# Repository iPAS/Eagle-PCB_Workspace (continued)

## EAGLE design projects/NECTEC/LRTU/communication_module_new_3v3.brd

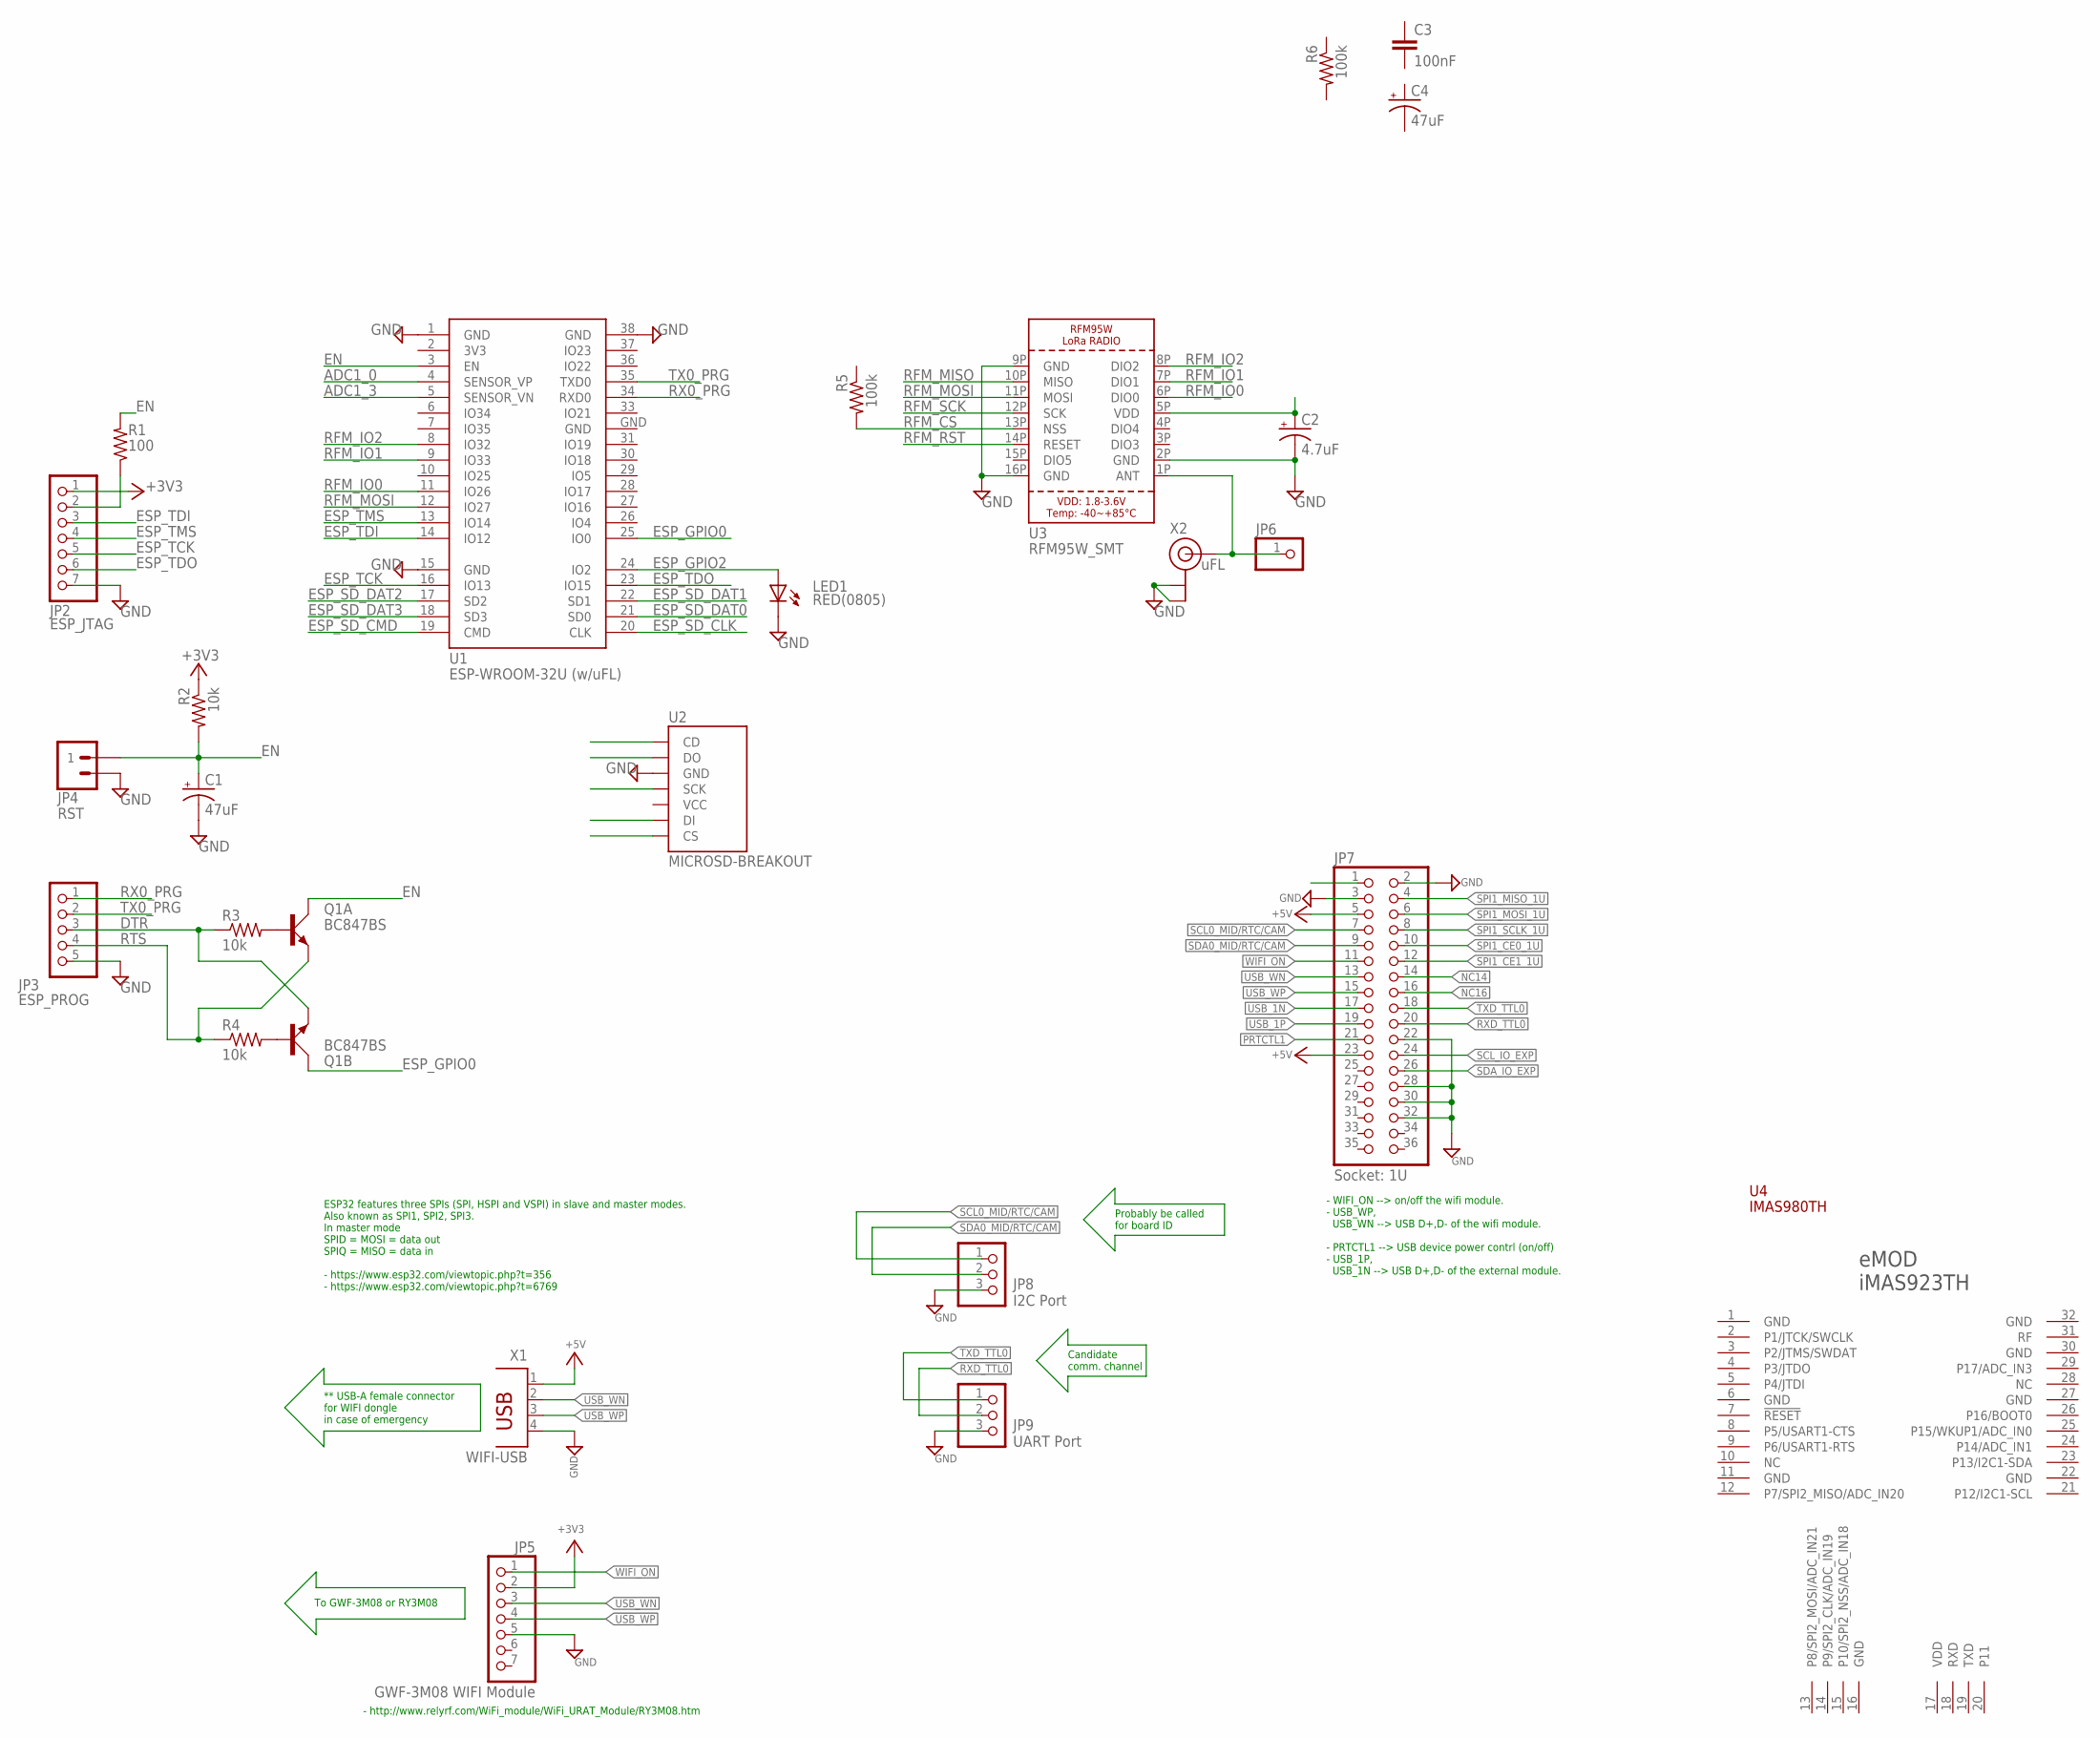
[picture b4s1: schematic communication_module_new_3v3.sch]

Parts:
C1, C4: 47uF; RCL_150CLZ-1014
C2: 4.7uF; RCL_150CLZ-1014
C3: 100nF; RCL_C1206
JP2: ESP_JTAG; 1X07
JP3: ESP_PROG; 1X05
JP4: RST; 1X02
JP5: GWF-3M08 WIFI Module; 1X07
JP6: HEADER-1X1ROUND; 1X01_ROUND
JP7: Socket: 1U; 2X18
JP8: I2C Port; 1X03
JP9: UART Port; 1X03
LED1: RED(0805); CHIP-LED0805
Q1: BC847BS; SOT363_PHILIPS
R1: 100; RCL_M0805
R2, R3, R4: 10k; RCL_M0805
R5, R6: 100k; RCL_M0805
U1: ESP-WROOM-32U (w/uFL); ESP-WROOM-32
U2: MICROSD-BREAKOUT
U3: RFM95W_SMT; RFMHCW_SMT
U4: IMAS980TH; IMAS923TH
X1: WIFI-USB; PN87520
X2: uFL; U.FL

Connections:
3V3: U1.2 (3V3)
+3V3: JP2.1, JP5.2, R2.1
+5V: JP7.5, JP7.23, X1.1
ADC1_0: U1.4 (SENSOR_VP)
ADC1_3: U1.5 (SENSOR_VN)
ANT: JP6.1, U3.1P (ANT), X2.3 (SIGNAL)
DTR: JP3.3, Q1.4 (E), R3.1
EN: C1.+, JP4.1, Q1.6 (C), R1.2, R2.2, U1.3 (EN)
ESP_GPIO0: Q1.3 (C), U1.25 (IO0)
ESP_GPIO2: LED1.A, U1.24 (IO2)
ESP_SD_CLK: U1.20 (CLK)
ESP_SD_CMD: U1.19 (CMD)
ESP_SD_DAT0: U1.21 (SD0)
ESP_SD_DAT1: U1.22 (SD1)
ESP_SD_DAT2: U1.17 (SD2)
ESP_SD_DAT3: U1.18 (SD3)
ESP_TCK: JP2.5, U1.16 (IO13)
ESP_TDI: JP2.3, U1.14 (IO12)
ESP_TDO: JP2.6, U1.23 (IO15)
ESP_TMS: JP2.4, U1.13 (IO14)
GND: C1.-, C2.-, JP2.7, JP3.5, JP4.2, JP5.5, JP7.2, JP7.3, JP7.22, JP7.28, JP7.30, JP7.32, JP8.3, JP9.3, LED1.C, U1.1 (GND), U1.15 (GND), U1.38 (GND), U1.GND, U2.GND, U3.2P (GND), U3.9P (GND), U3.16P (GND), U4.1 (GND), U4.6 (GND), U4.11 (GND), U4.16 (GND), U4.22 (GND), U4.27 (GND), U4.30 (GND), U4.32 (GND), X1.4, X2.1 (GND), X2.2 (GND)
unnamed: C2.+, U3.5P (VDD)
unnamed: Q1.2 (B), R3.2
unnamed: Q1.5 (B), R4.2
unnamed: JP2.2, R1.1
NC14: JP7.14
NC16: JP7.16
PRTCTL1: JP7.21
RFM_CS: R5.2, U3.13P (NSS)
RFM_IO0: U1.11 (IO26), U3.6P (DIO0)
RFM_IO1: U1.9 (IO33), U3.7P (DIO1)
RFM_IO2: U1.8 (IO32), U3.8P (DIO2)
RFM_MISO: U3.10P (MISO)
RFM_MOSI: U1.12 (IO27), U3.11P (MOSI)
RFM_RST: U3.14P (RESET)
RFM_SCK: U3.12P (SCK)
RTS: JP3.4, Q1.1 (E), R4.1
RX0_PRG: JP3.1, U1.34 (RXD0)
RXD_TTL0: JP7.20, JP9.2
SCL0_MID/RTC/CAM: JP7.7, JP8.1
SCL_IO_EXP: JP7.24
SDA0_MID/RTC/CAM: JP7.9, JP8.2
SDA_IO_EXP: JP7.26
SPI1_CE0_1U: JP7.10
SPI1_CE1_1U: JP7.12
SPI1_MISO_1U: JP7.4
SPI1_MOSI_1U: JP7.6
SPI1_SCLK_1U: JP7.8
TX0_PRG: JP3.2, U1.35 (TXD0)
TXD_TTL0: JP7.18, JP9.1
USB_1N: JP7.17
USB_1P: JP7.19
USB_WN: JP5.3, JP7.13, X1.2
USB_WP: JP5.4, JP7.15, X1.3
VDD: U4.17 (VDD)
WIFI_ON: JP5.1, JP7.11

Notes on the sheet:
ESP32 features three SPIs (SPI, HSPI and VSPI) in slave and master modes. Also known as SPI1, SPI2, SPI3. In master mode SPID = MOSI = data out SPIQ = MISO = data in - https://www.esp32.com/viewtopic.php?t=356 - https://www.esp32.com/viewtopic.php?t=6769
- WIFI_ON --> on/off the wifi module. - USB_WP, USB_WN --> USB D+,D- of the wifi module. - PRTCTL1 --> USB device power contrl (on/off) - USB_1P, USB_1N --> USB D+,D- of the external module.
** USB-A female connector for WIFI dongle in case of emergency
Probably be called for board ID
Candidate comm. channel
To GWF-3M08 or RY3M08
- http://www.relyrf.com/WiFi_module/WiFi_URAT_Module/RY3M08.htm

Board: 2 copper layers, 26 parts (0 on the bottom side), 31 nets, no tracks yet.

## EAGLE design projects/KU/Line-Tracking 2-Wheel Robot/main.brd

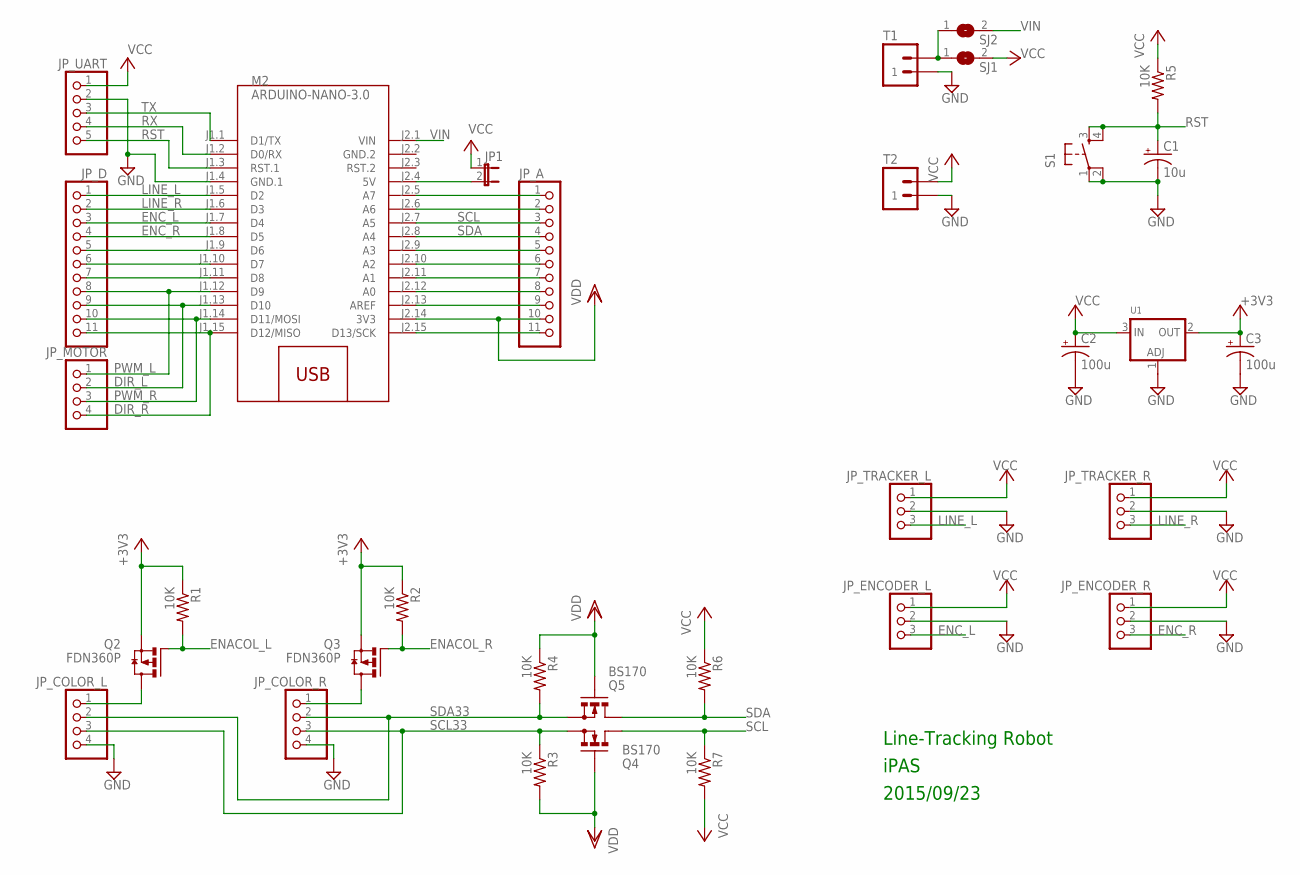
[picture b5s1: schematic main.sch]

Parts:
C1: 10u; RCL_E2,5-6
C2, C3: 100u; RCL_E2,5-6
JP1: JUMPER2
JP_A: HEADER-1X11; 1X11_ROUND
JP_COLOR_L: HEADER-1X4ROUND; 1X04_ROUND
JP_COLOR_R: HEADER-1X4ROUND; 1X04_ROUND
JP_D: HEADER-1X11; 1X11_ROUND
JP_ENCODER_L: HEADER-1X3ROUND; 1X03_ROUND
JP_ENCODER_R: HEADER-1X3ROUND; 1X03_ROUND
JP_MOTOR: HEADER-1X4ROUND; 1X04_ROUND
JP_TRACKER_L: HEADER-1X3ROUND; 1X03_ROUND
JP_TRACKER_R: HEADER-1X3ROUND; 1X03_ROUND
JP_UART: HEADER-1X5ROUND; 1X05_ROUND
M2: ARDUINO-NANO-3.0
Q2, Q3: FDN360P; SUPER-SOT3
Q4, Q5: BS170; TO92-
R1, R2, R3, R4, R5, R6, R7: 10K; RCL_0204/5
S1: SWITCH-TACT_DTS-6
SJ1, SJ2: SOLDERJUMPERREFLOW; SOLDERJUMPER_REFLOW
T1, T2: ST02-3.81MM; DG381-02P
U1: LM1117SOT223-REFLOW; SOT223-R

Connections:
+3V3: C3.+, Q2.2 (S), Q3.2 (S), R1.1, R2.1, U1.2 (OUT)
DIR_L: JP_D.9, JP_MOTOR.2, M2.J1.13 (D10)
DIR_R: JP_D.11, JP_MOTOR.4, M2.J1.15 (D12/MISO)
ENACOL_L: Q2.1 (G), R1.2
ENACOL_R: Q3.1 (G), R2.2
ENC_L: JP_D.3, JP_ENCODER_L.3, M2.J1.7 (D4)
ENC_R: JP_D.4, JP_ENCODER_R.3, M2.J1.8 (D5)
GND: C1.-, C2.-, C3.-, JP_COLOR_L.4, JP_COLOR_R.4, JP_ENCODER_L.2, JP_ENCODER_R.2, JP_TRACKER_L.2, JP_TRACKER_R.2, JP_UART.2, M2.J1.4 (GND.1), S1.1, S1.2, T1.1, T2.1, U1.1 (ADJ)
GND.2: M2.J2.2 (GND.2)
LINE_L: JP_D.1, JP_TRACKER_L.3, M2.J1.5 (D2)
LINE_R: JP_D.2, JP_TRACKER_R.3, M2.J1.6 (D3)
unnamed: JP_COLOR_R.1, Q3.3 (D)
unnamed: JP_A.1, M2.J2.5 (A7)
unnamed: JP_COLOR_L.1, Q2.3 (D)
unnamed: JP_A.2, M2.J2.6 (A6)
unnamed: JP1.2, M2.J2.4 (5V)
unnamed: SJ1.1, SJ2.1, T1.2
unnamed: JP_D.5, M2.J1.9 (D6)
unnamed: JP_D.6, M2.J1.10 (D7)
unnamed: JP_D.7, M2.J1.11 (D8)
unnamed: JP_A.5, M2.J2.9 (A3)
unnamed: JP_A.6, M2.J2.10 (A2)
unnamed: JP_A.7, M2.J2.11 (A1)
unnamed: JP_A.8, M2.J2.12 (A0)
unnamed: JP_A.9, M2.J2.13 (AREF)
unnamed: JP_A.11, M2.J2.15 (D13/SCK)
PWM_L: JP_D.8, JP_MOTOR.1, M2.J1.12 (D9)
PWM_R: JP_D.10, JP_MOTOR.3, M2.J1.14 (D11/MOSI)
RST: C1.+, JP_UART.5, M2.J1.3 (RST.1), R5.2, S1.3, S1.4
RX: JP_UART.4, M2.J1.2 (D0/RX)
SCL: JP_A.3, M2.J2.7 (A5), Q4.1 (D), R7.1
SCL33: JP_COLOR_L.3, JP_COLOR_R.3, Q4.3 (S), R3.1
SDA: JP_A.4, M2.J2.8 (A4), Q5.1 (D), R6.2
SDA33: JP_COLOR_L.2, JP_COLOR_R.2, Q5.3 (S), R4.2
TX: JP_UART.3, M2.J1.1 (D1/TX)
VCC: C2.+, JP1.1, JP_ENCODER_L.1, JP_ENCODER_R.1, JP_TRACKER_L.1, JP_TRACKER_R.1, JP_UART.1, R5.1, R6.1, R7.2, SJ1.2, T2.2, U1.3 (IN)
VDD: JP_A.10, M2.J2.14 (3V3), Q4.2 (G), Q5.2 (G), R3.2, R4.1
VIN: M2.J2.1 (VIN), SJ2.2

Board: 2 copper layers, 32 parts (0 on the bottom side), 37 nets, no tracks yet.

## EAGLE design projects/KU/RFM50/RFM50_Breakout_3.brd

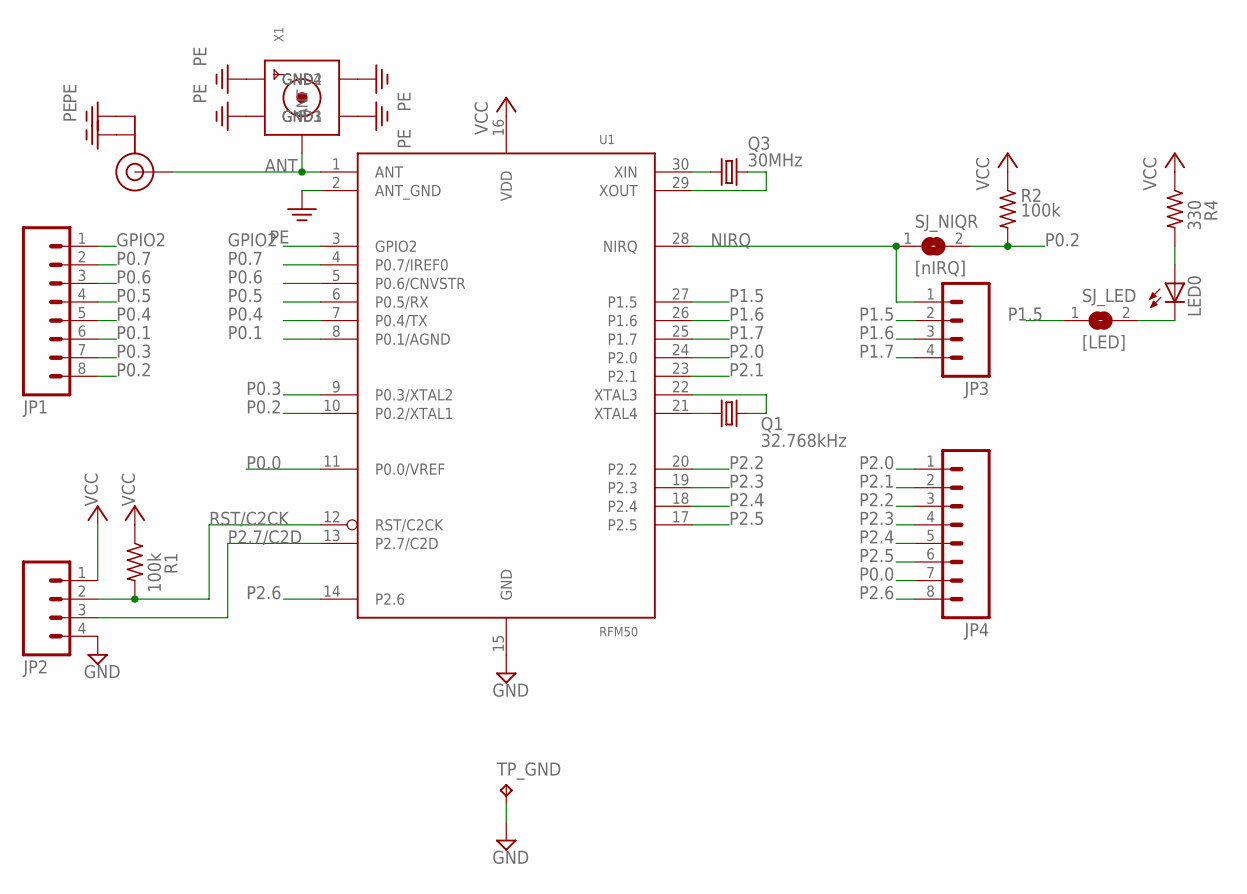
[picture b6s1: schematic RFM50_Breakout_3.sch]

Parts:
JP1, JP4: M081X08; 1X08
JP2, JP3: M04PTH; 1X04
LED0: LED3MM
Q1: 32.768kHz; TC26H
Q3: 30MHz; HC49/S
R1: 100k; RCL_0204/7
R2: 100k; RCL_M1206
R4: 330; RCL_0204/5
SJ_LED: [LED]; SOLDERJUMPER_REFLOW
SJ_NIQR: [nIRQ]; SOLDERJUMPER_REFLOW
TP_GND: TPPAD1-10; P1-10_TP
U1: RFM50
U$1: U.FL
X1: SMACONNECTOR; SMA90_DIP

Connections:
ANT: U1.1 (ANT), U$1.P$3 (SIGNAL), X1.ANTENNA (ANT)
GND: JP2.4, TP_GND.TP, U1.15 (GND)
GPIO2: JP1.1, U1.3 (GPIO2)
unnamed: LED0.A, R4.2
unnamed: LED0.K (C), SJ_LED.2
unnamed: Q1.1, U1.21 (XTAL4)
unnamed: Q3.1, U1.30 (XIN)
unnamed: Q3.2, U1.29 (XOUT)
unnamed: Q1.2, U1.22 (XTAL3)
NIRQ: JP3.1, SJ_NIQR.1, U1.28 (NIRQ)
P0.0: JP4.7, U1.11 (P0.0/VREF)
P0.1: JP1.6, U1.8 (P0.1/AGND)
P0.2: JP1.8, R2.2, SJ_NIQR.2, U1.10 (P0.2/XTAL1)
P0.3: JP1.7, U1.9 (P0.3/XTAL2)
P0.4: JP1.5, U1.7 (P0.4/TX)
P0.5: JP1.4, U1.6 (P0.5/RX)
P0.6: JP1.3, U1.5 (P0.6/CNVSTR)
P0.7: JP1.2, U1.4 (P0.7/IREF0)
P1.5: JP3.2, SJ_LED.1, U1.27 (P1.5)
P1.6: JP3.3, U1.26 (P1.6)
P1.7: JP3.4, U1.25 (P1.7)
P2.0: JP4.1, U1.24 (P2.0)
P2.1: JP4.2, U1.23 (P2.1)
P2.2: JP4.3, U1.20 (P2.2)
P2.3: JP4.4, U1.19 (P2.3)
P2.4: JP4.5, U1.18 (P2.4)
P2.5: JP4.6, U1.17 (P2.5)
P2.6: JP4.8, U1.14 (P2.6)
P2.7/C2D: JP2.3, U1.13 (P2.7/C2D)
PE: U1.2 (ANT_GND), U$1.P$1 (GND), U$1.P$2 (GND), X1.GND1, X1.GND2, X1.GND3, X1.GND4
RST/C2CK: JP2.2, R1.2, U1.12 (RST/C2CK)
VCC: JP2.1, R1.1, R2.1, R4.1, U1.16 (VDD)

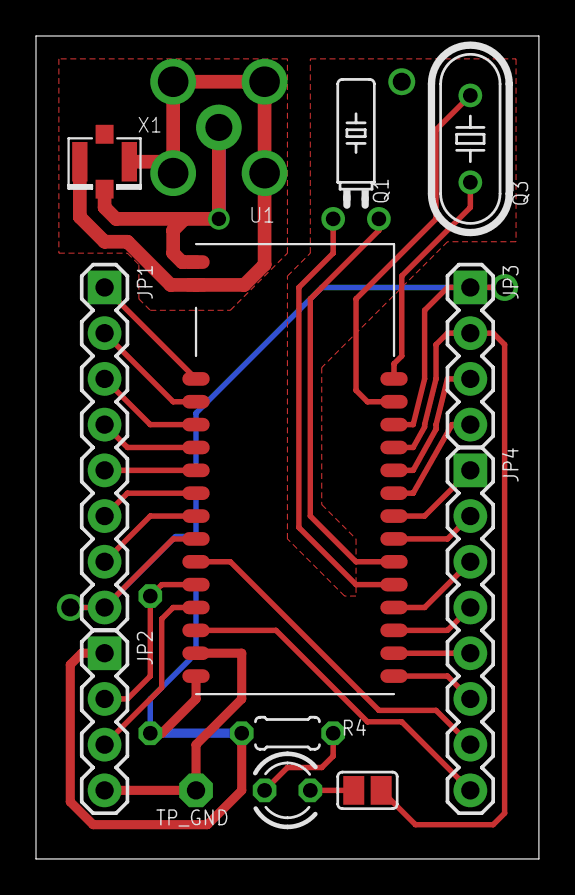
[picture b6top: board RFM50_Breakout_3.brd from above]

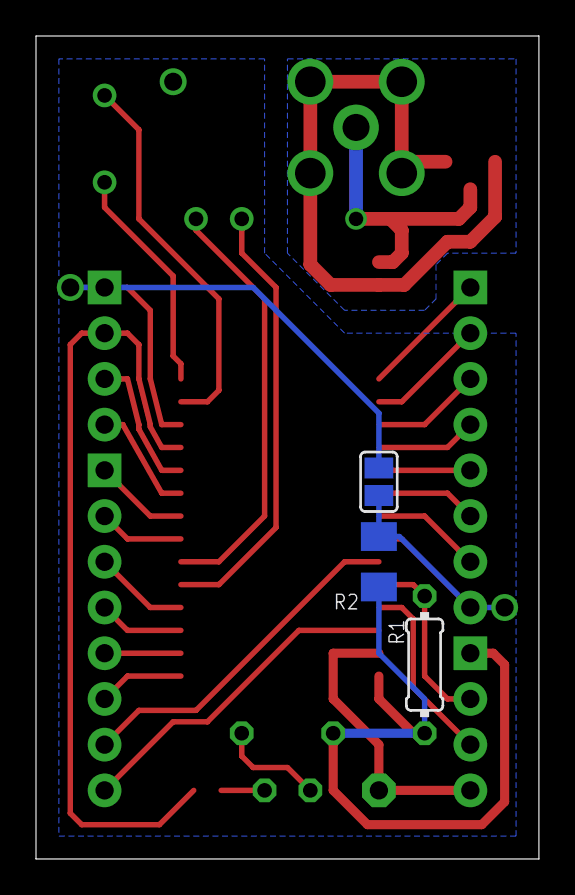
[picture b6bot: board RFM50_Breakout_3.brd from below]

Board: 2 copper layers, 27.9 x 45.7 mm, 16 parts (3 on the bottom side), 32 nets.

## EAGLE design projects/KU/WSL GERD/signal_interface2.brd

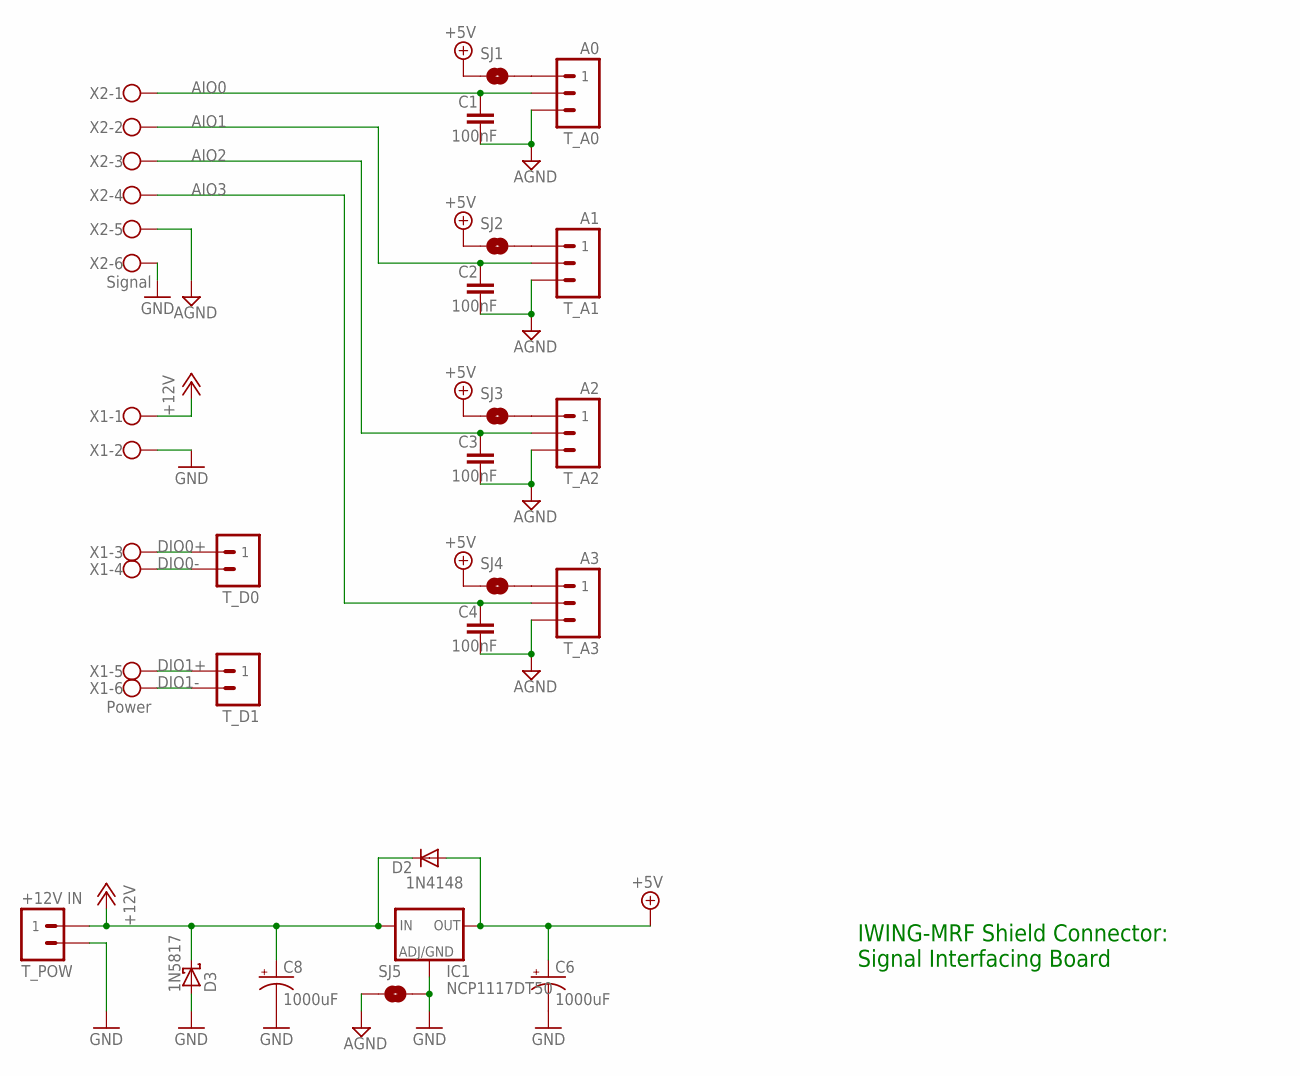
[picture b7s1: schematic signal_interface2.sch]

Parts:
C1, C2, C3, C4: 100nF; RCL_C050-025X075
C6, C8: 1000uF; RCL_E5-13
D2: 1N4148; DO35-100V
D3: 1N5817; DO41-150V
IC1: NCP1117DT50; DPACK
SJ1, SJ2, SJ3, SJ4: SOLDERJUMPERNC; SJ_2S
SJ5: SOLDERJUMPERTRACE; SJ_2S-TRACE
T_A0: A0; EK500V-03P
T_A1: A1; EK500V-03P
T_A2: A2; EK500V-03P
T_A3: A3; EK500V-03P
T_D0, T_D1: ST02-5MM; EK500V-02P
T_POW: +12V IN; EK500V-02P
X1: Power; 5EHDRC-6P
X2: Signal; 5EHDRC-6P

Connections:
+5V: C6.+, D2.A, IC1.4 (OUT), SJ1.1, SJ2.1, SJ3.1, SJ4.1
+12V: C8.+, D2.C, D3.C, IC1.3 (IN), T_POW.P$1 (1), X1.1
AGND: C1.2, C2.2, C3.2, C4.2, SJ5.1, T_A0.P$3 (3), T_A1.P$3 (3), T_A2.P$3 (3), T_A3.P$3 (3), X2.5
AIO0: C1.1, T_A0.P$2 (2), X2.1
AIO1: C2.1, T_A1.P$2 (2), X2.2
AIO2: C3.1, T_A2.P$2 (2), X2.3
AIO3: C4.1, T_A3.P$2 (2), X2.4
DIO0+: T_D0.P$1 (1), X1.3
DIO0-: T_D0.P$2 (2), X1.4
DIO1+: T_D1.P$1 (1), X1.5
DIO1-: T_D1.P$2 (2), X1.6
GND: C6.-, C8.-, D3.A, IC1.1 (ADJ), SJ5.2, T_POW.P$2 (2), X1.2, X2.6
unnamed: SJ1.2, T_A0.P$1 (1)
unnamed: SJ2.2, T_A1.P$1 (1)
unnamed: SJ3.2, T_A2.P$1 (1)
unnamed: SJ4.2, T_A3.P$1 (1)

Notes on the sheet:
IWING-MRF Shield Connector: Signal Interfacing Board

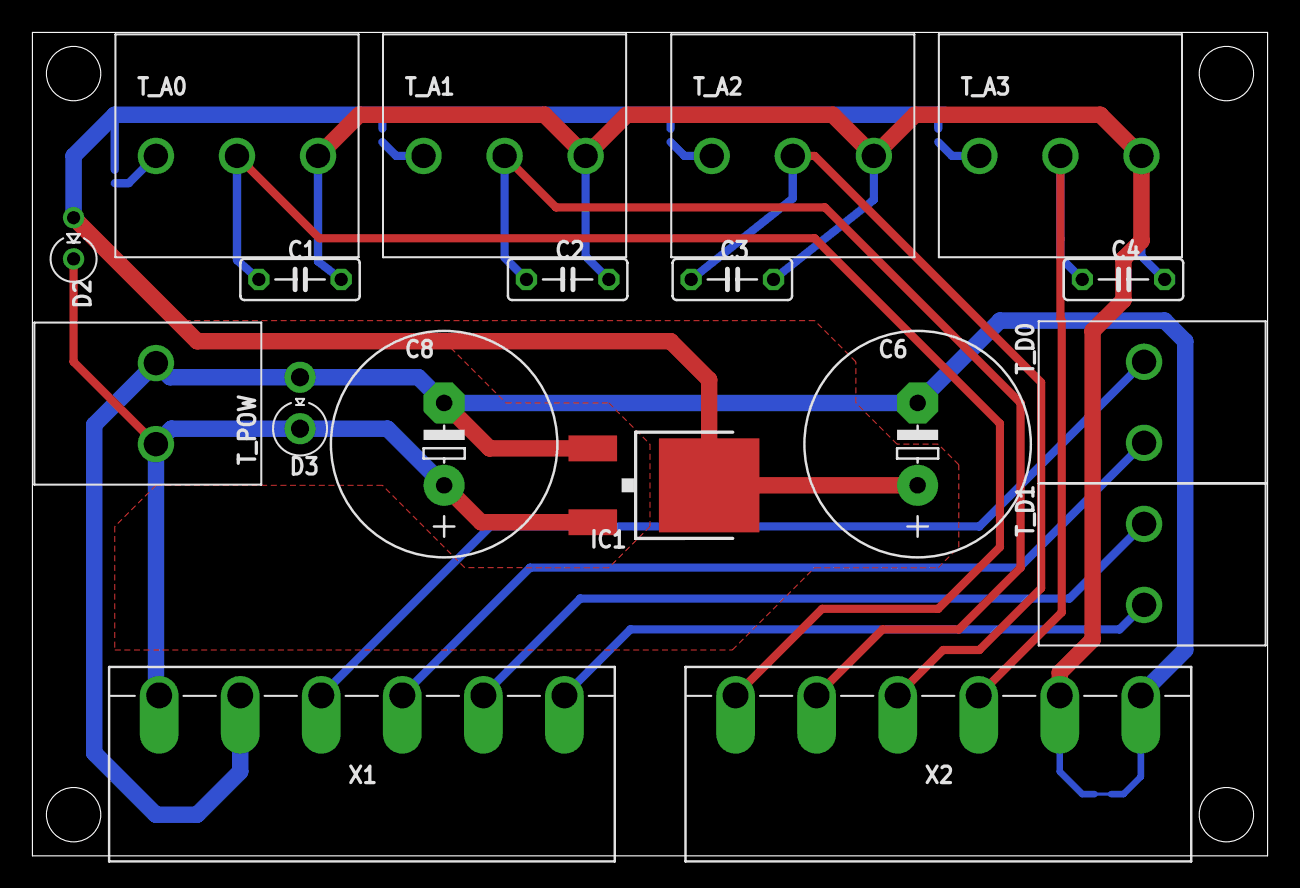
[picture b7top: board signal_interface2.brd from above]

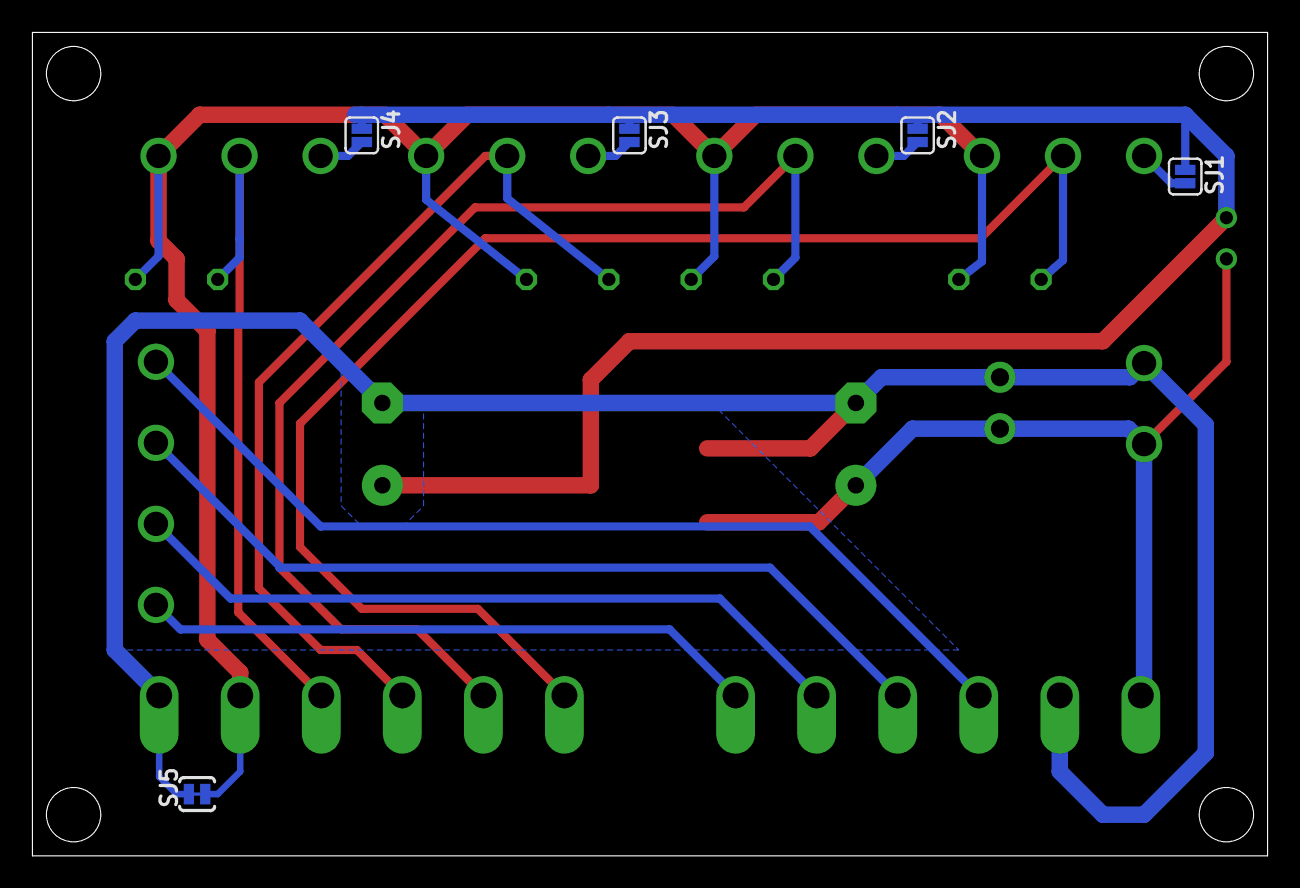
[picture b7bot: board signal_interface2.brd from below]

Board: 2 copper layers, 76.2 x 50.8 mm, 23 parts (5 on the bottom side), 16 nets.

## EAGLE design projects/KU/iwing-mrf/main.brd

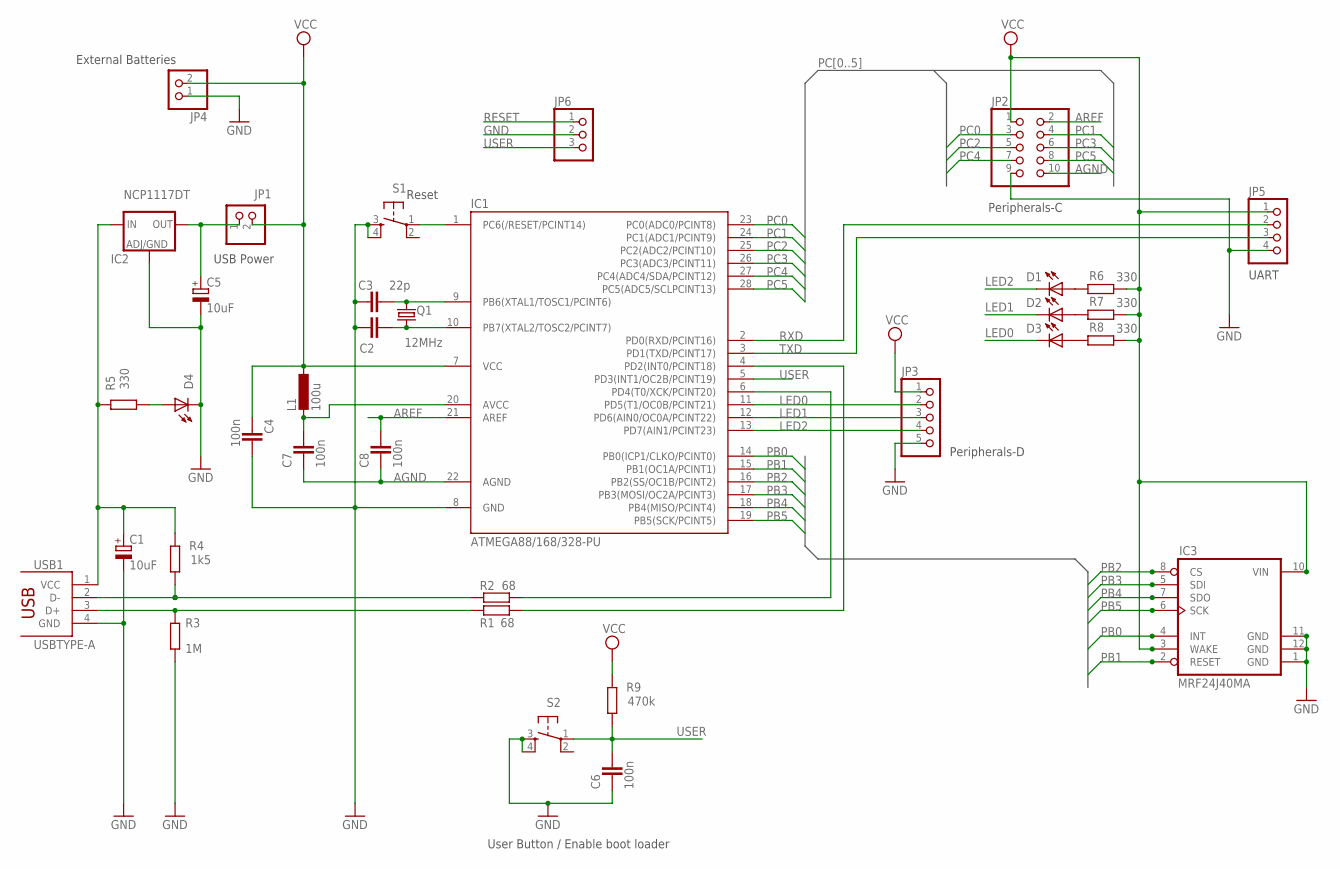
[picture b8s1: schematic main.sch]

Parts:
C1, C5: 10uF; E2,5-6E
C2, C3: 22p; C025-024X044
C4, C6, C7, C8: 100n; C050-024X044
D1, D2, D3, D4: LED3MM
IC1: ATMEGA88/168/328-PU; DIL28-3
IC2: NCP1117DT; DPACK
IC3: MRF24J40MA/B/C; MRF24J40MAB-TH
JP1, JP4: PINHD-1X2; 1X02
JP2: HEADER-2X5; 2X05
JP3: PINHD-1X5; 1X05
JP5: HEADER-1X4ROUND; 1X04_ROUND
JP6: PINHD-1X3; 1X03
L1: 100u; 0207/7
Q1: 12MHz; HC49/S
R1, R2: 68; 0204/5@1
R3: 1M; 0204/5@1
R4: 1k5; 0204/5@1
R5: 330; 0204/7@1
R6, R7, R8: 330; 0204/5@1
R9: 470k; 0204/5@1
S1, S2: DTS-6
USB1: USBTYPE-A

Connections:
AGND: C7.1, C8.1, IC1.22 (AGND), JP2.10
AREF: C8.2, IC1.21 (AREF), JP2.2
D+: R1.1, R3.2, USB1.3 (D+)
D-: R2.1, R4.2, USB1.2 (D-)
GND: C1.-, C2.1, C3.1, C4.2, C5.-, C6.1, D4.K (C), IC1.8 (GND), IC2.1 (ADJ), IC3.1 (GND), IC3.11 (GND), IC3.12 (GND), IC3.13 (GND), IC3.23 (GND), IC3.24 (GND), JP2.9, JP3.5, JP4.1, JP5.4, JP6.2, R3.1, S1.3, S1.4, S2.3, S2.4, USB1.4 (GND)
LED0: D3.K (C), IC1.11 (PD5(T1/OC0B/PCINT21)), JP3.2
LED1: D2.K (C), IC1.12 (PD6(AIN0/OC0A/PCINT22)), JP3.3
LED2: D1.K (C), IC1.13 (PD7(AIN1/PCINT23)), JP3.4
unnamed: IC1.4 (PD2(INT0/PCINT18)), R1.2
unnamed: IC1.6 (PD4(T0/XCK/PCINT20)), R2.2
unnamed: C5.+, IC2.4 (OUT), JP1.1
unnamed: D1.A, R6.2
unnamed: C7.2, IC1.20 (AVCC), L1.1
unnamed: D2.A, R7.2
unnamed: D3.A, R8.2
unnamed: C2.2, IC1.10 (PB7(XTAL2/TOSC2/PCINT7)), Q1.1
unnamed: C3.2, IC1.9 (PB6(XTAL1/TOSC1/PCINT6)), Q1.2
unnamed: C1.+, IC2.3 (IN), R4.1, R5.1, USB1.1 (VCC)
unnamed: D4.A, R5.2
PB0: IC1.14 (PB0(ICP1/CLKO/PCINT0)), IC3.4 (INT), IC3.16 (INT)
PB1: IC1.15 (PB1(OC1A/PCINT1)), IC3.2 (RESET), IC3.14 (RESET)
PB2: IC1.16 (PB2(SS/OC1B/PCINT2)), IC3.8 (CS), IC3.20 (CS)
PB3: IC1.17 (PB3(MOSI/OC2A/PCINT3)), IC3.5 (SDI), IC3.17 (SDI)
PB4: IC1.18 (PB4(MISO/PCINT4)), IC3.7 (SDO), IC3.19 (SDO)
PB5: IC1.19 (PB5(SCK/PCINT5)), IC3.6 (SCK), IC3.18 (SCK)
PC0: IC1.23 (PC0(ADC0/PCINT8)), JP2.3
PC1: IC1.24 (PC1(ADC1/PCINT9)), JP2.4
PC2: IC1.25 (PC2(ADC2/PCINT10)), JP2.5
PC3: IC1.26 (PC3(ADC3/PCINT11)), JP2.6
PC4: IC1.27 (PC4(ADC4/SDA/PCINT12)), JP2.7
PC5: IC1.28 (PC5(ADC5/SCLPCINT13)), JP2.8
RESET: IC1.1 (PC6(/RESET/PCINT14)), JP6.1, S1.1
RXD: IC1.2 (PD0(RXD/PCINT16)), JP5.2
TXD: IC1.3 (PD1(TXD/PCINT17)), JP5.3
USER: C6.2, IC1.5 (PD3(INT1/OC2B/PCINT19)), JP6.3, R9.2, S2.1
VCC: C4.1, IC1.7 (VCC), IC3.3 (WAKE), IC3.10 (VIN), IC3.15 (WAKE), IC3.22 (VIN), JP1.2, JP2.1, JP3.1, JP4.2, JP5.1, L1.2, R6.1, R7.1, R8.1, R9.1

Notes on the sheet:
User Button / Enable boot loader
Reset
External Batteries
UART
Peripherals-C
USB Power
Peripherals-D

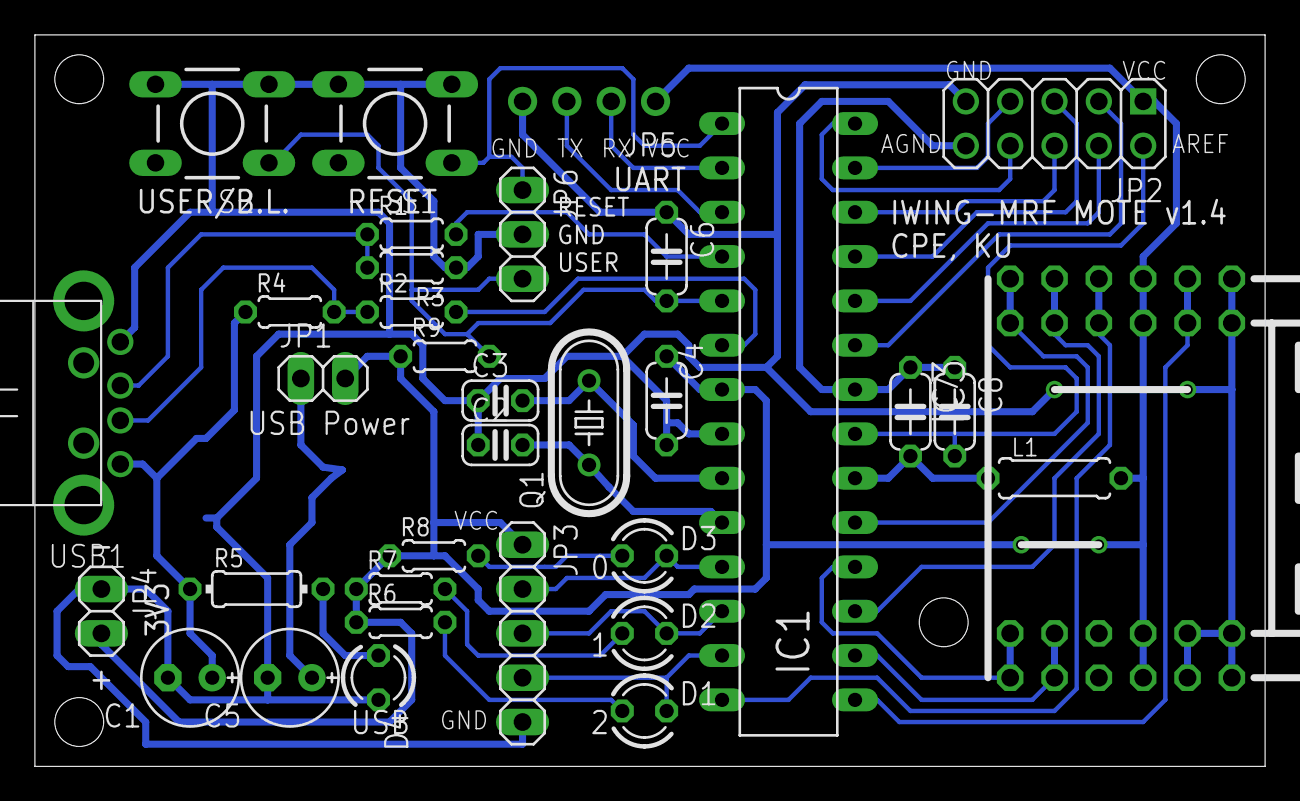
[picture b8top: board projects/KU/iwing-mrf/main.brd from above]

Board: 2 copper layers, 70.5 x 41.9 mm, 35 parts (1 on the bottom side), 36 nets.

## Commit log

2019-06-24 Init
2019-06-24 Readd submodules.
2019-08-05 Add new libraries for RPi and Beagle.
2019-08-05 Fix ESP-eMOD connection, adding pull-up and swap uart pins.
2019-08-05 Init INCT2019 LRTU board project.
2019-08-05 Add submodule as a guide for CM3 project design.
2019-08-16 New design communication_module_to_aj-doy
2019-08-19 Change font-size for better printing.
2019-08-19 Change names for better tracking.
2019-08-19 Make for printing.
2019-08-19 Update the communication board design, and, make PDFs.
2019-08-19 Start designing the new NICT project.
2019-08-21 Almost finished the ESP32-CM3 design.
2019-08-22 Complete the CM3-ESP32 board roughly.
2019-09-16 Add libraries.
2019-09-16 Revise many things after dealing with Aj.Doy.
2020-08-11 Backup projects
2020-09-21 Save
2020-09-21 Backup NECTEC projects
2020-09-21 Remove unused
2020-12-05 New design for USB-RS232
2020-12-05 Project update to the new version of Eagle
2021-10-17 Prepare NEW RTU platform on 2022
